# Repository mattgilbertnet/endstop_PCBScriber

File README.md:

# endstop_PCBScriber

This project has been moved to GitLab: https://gitlab.com/mattgilbertnet/endstop_PCBScriber

Optical Endstop designed for PCBScriber, designed in KiCad

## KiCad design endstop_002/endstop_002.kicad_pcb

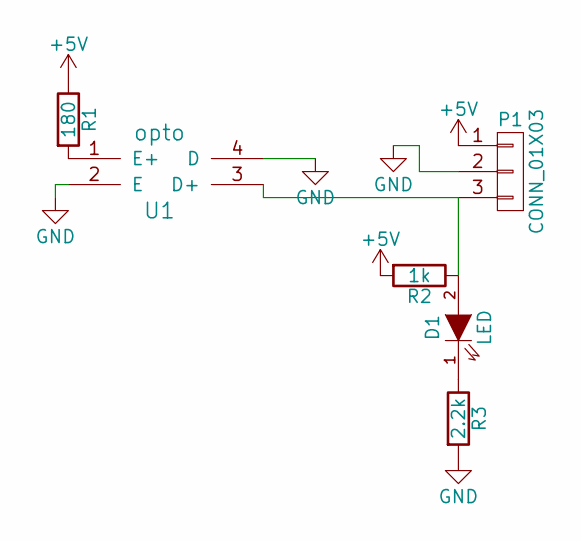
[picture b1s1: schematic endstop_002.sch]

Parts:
D1: LED; LED-5MM
P1: CONN_01X03; conn3
R1: 180; R_1206_HandSoldering
R2: 1k; R_0805_HandSoldering
R3: 2.2k; R_1206_HandSoldering
U1: opto; opto_endstops

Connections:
+5V: P1.1, R1.1, R2.2
GND: P1.2, R3.2, U1.2 (E), U1.4 (D)
unnamed: D1.1 (K), R3.1
unnamed: D1.2 (A), P1.3, R2.1, U1.3 (D+)
unnamed: R1.2, U1.1 (E+)

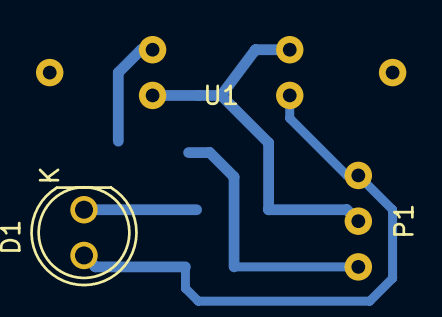
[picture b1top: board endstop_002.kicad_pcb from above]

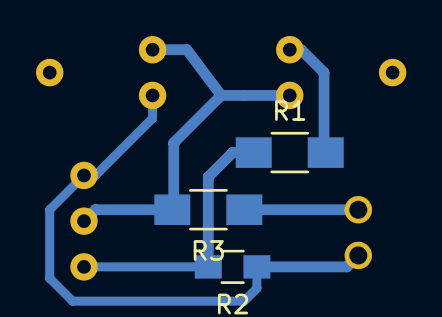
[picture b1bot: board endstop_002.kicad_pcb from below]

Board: 2 copper layers, 6 parts (3 on the bottom side), 5 nets.
